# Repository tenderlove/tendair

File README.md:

# Tendair

Tendair is a CO2 / Temp / RH / PM2.5 / VOC / NOx sensor hooked up to an ESP32.

It's basically just [this sensor](https://sensirion.com/media/documents/FAFC548D/693FBB15/PS_DS_SEN6x.pdf)
with [this micro controller](https://www.digikey.com/en/products/detail/espressif-systems/ESP32-C3-WROOM-02-H4/14553033)

Here is a photo:

This is basically just a new version of my [ESP8266 AQ sensor](https://github.com/tenderlove/esp8266aq).

I haven't made an enclosure yet, I'm working on that now.

## Flashing with ESPHome

`esphome.yml` configures the board for [ESPHome](https://esphome.io).
To use the ESP-IDF firmware instead, see [firmware/README.md](firmware/README.md).

Create `secrets.yaml` next to `esphome.yml` with the following keys:

```yaml
wifi_ssid: "your network"
wifi_password: "your wifi password"
api_encryption_key: "output of openssl rand -base64 32"
ap_password: "password for the fallback hotspot"
```

The USB-C port only supplies power, so the first flash goes through a
USB-serial adapter on the 6-pin header. Wire the adapter's TX to the board's
RXD and its RX to TXD, then run:

```
esphome -s name tendair-office run esphome.yml
```

The `-s name` flag sets the device's hostname, which defaults to `tendair`.
Pass the same name on every flash, or the board gets renamed. After the first
flash, `esphome run` can update the board over Wi-Fi.

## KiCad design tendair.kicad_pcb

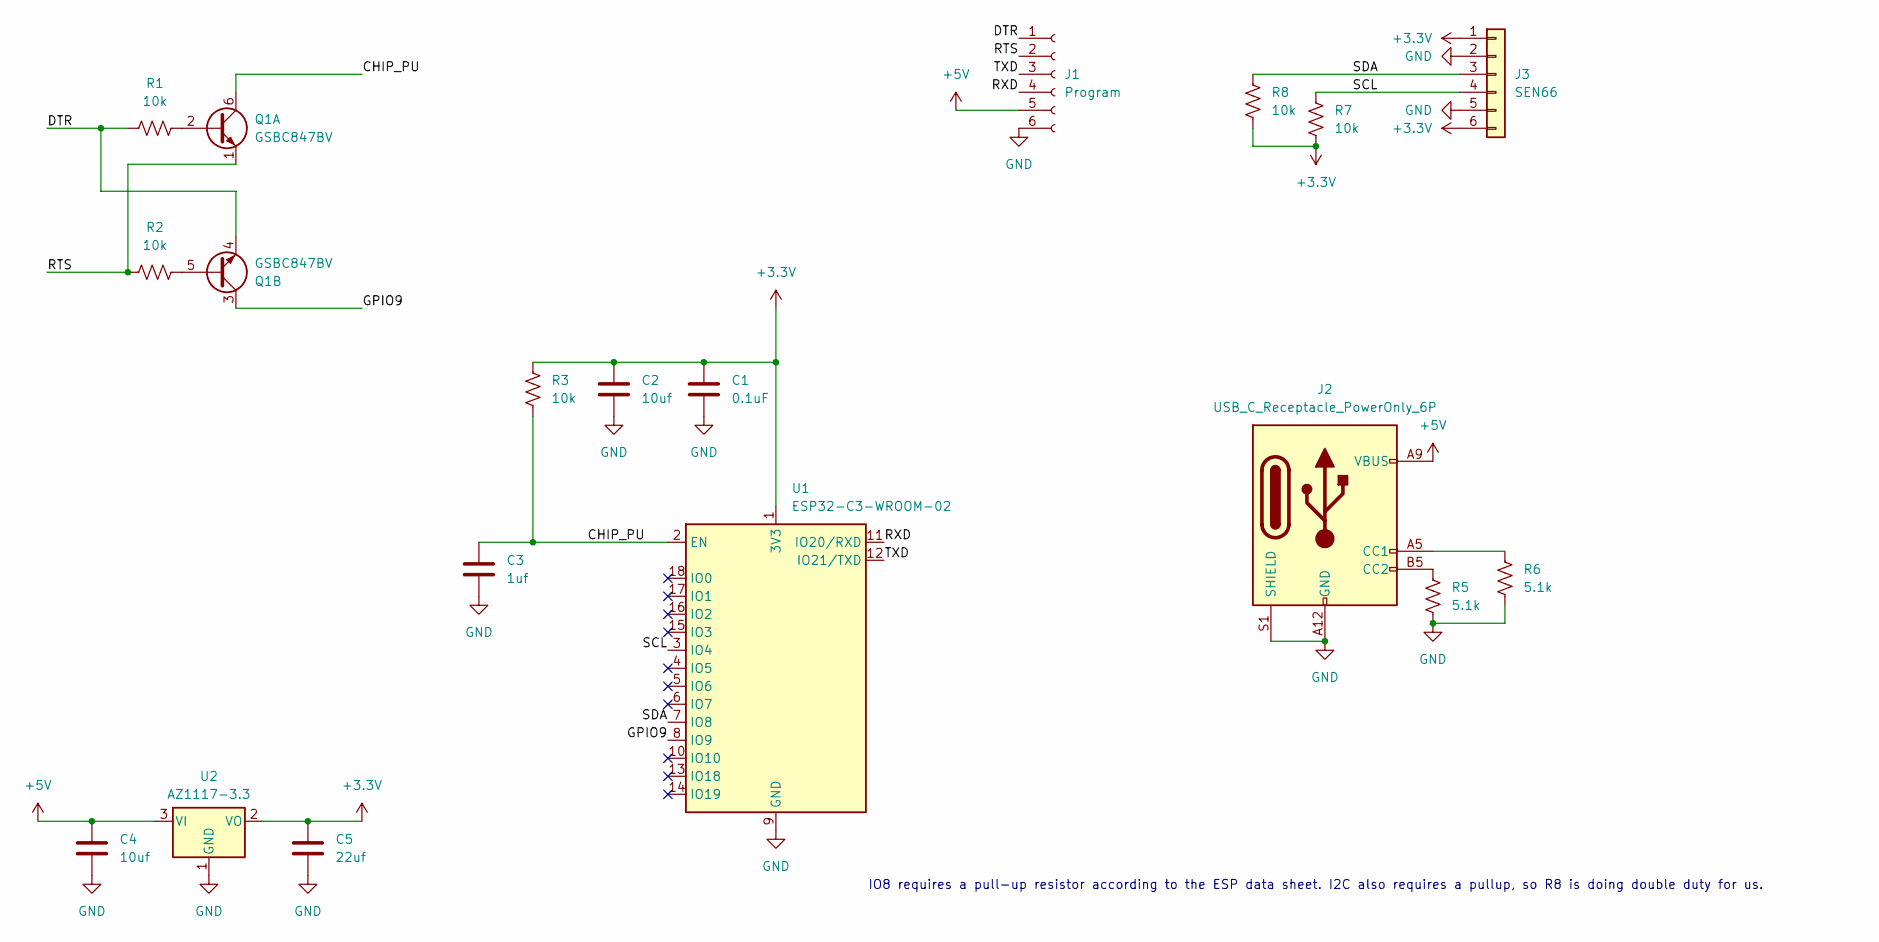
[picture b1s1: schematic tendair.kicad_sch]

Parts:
C1: 0.1uF; C_1206_3216Metric
C2, C4: 10uf; C_1206_3216Metric
C3: 1uf; C_1206_3216Metric
C5: 22uf; C_1206_3216Metric
J1: Program; PinHeader_1x06_P2.54mm_Vertical
J2: USB_C_Receptacle_PowerOnly_6P; USB_C_Receptacle_GCT_USB4125-xx-x_6P_TopMnt_Horizontal
J3: SEN66; JST_GH_SM06B-GHS-TB_1x06-1MP_P1.25mm_Horizontal
Q1: GSBC847BV; SOT-563
R1, R2, R3, R7, R8: 10k; R_1206_3216Metric
R5, R6: 5.1k; R_1206_3216Metric
U1: ESP32-C3-WROOM-02
U2: AZ1117-3.3; SOT-89-3

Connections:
+3.3V: C1.1, C2.1, C5.1, J3.1, J3.6, R3.1, R7.2, R8.2, U1.1 (3V3), U2.2 (VO)
+5V: C4.1, J1.5, J2.A9 (VBUS), J2.B9 (VBUS), U2.3 (VI)
/CHIP_PU: C3.1, Q1.6 (C1), R3.2, U1.2 (EN)
/DTR: J1.1, Q1.4 (E2), R1.1
/GPIO9: Q1.3 (C2), U1.8 (IO9)
/RTS: J1.2, Q1.1 (E1), R2.1
/RXD: J1.4, U1.11 (IO20/RXD)
/SCL: J3.4, R7.1, U1.3 (IO4)
/SDA: J3.3, R8.1, U1.7 (IO8)
/TXD: J1.3, U1.12 (IO21/TXD)
GND: C1.2, C2.2, C3.2, C4.2, C5.2, J1.6, J2.A12 (GND), J2.B12 (GND), J2.S1 (SHIELD), J3.2, J3.5, R5.2, R6.2, U1.9 (GND), U1.19 (GND), U2.1 (GND)
unnamed: J2.A5 (CC1), R6.1
unnamed: J2.B5 (CC2), R5.1
unnamed: Q1.2 (B1), R1.2
unnamed: Q1.5 (B2), R2.2

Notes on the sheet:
IO8 requires a pull-up resistor according to the ESP data sheet. I2C also requires a pullup, so R8 is doing double duty for us.

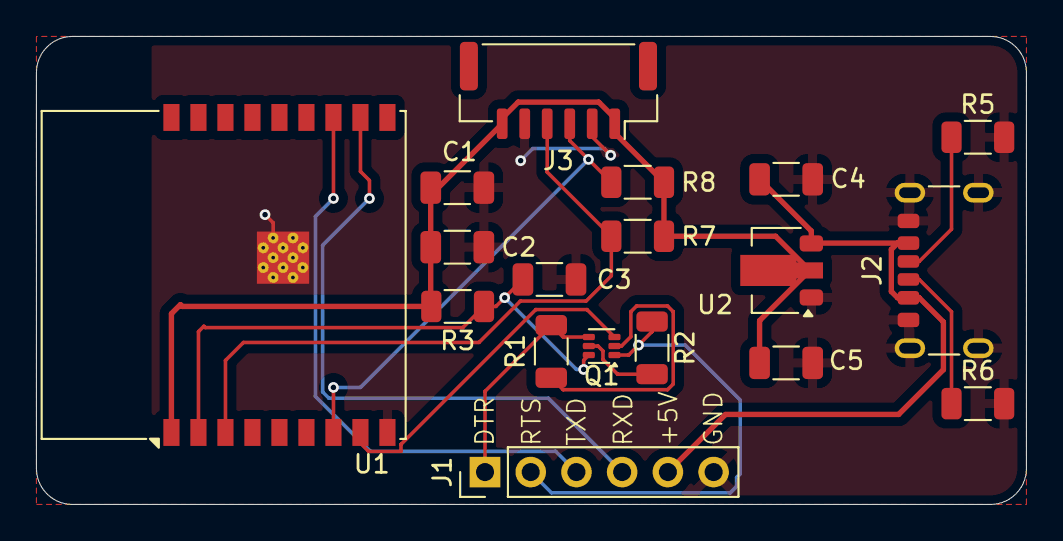
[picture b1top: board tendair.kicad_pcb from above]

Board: 2 copper layers, 55.0 x 26.0 mm, 18 parts (0 on the bottom side), 15 nets.

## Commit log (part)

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2025-11-08 initial schematics
2025-11-09 updating the pcb
2025-11-09 stuff
2025-11-10 seems good!
2025-11-16 adding image
2025-11-16 add license
2025-11-16 update schematic
2025-11-16 adding readme
2025-11-16 add some drawings
2025-11-22 adding bolt posts
2025-11-22 Happy with bolt posts
2025-11-23 Looking better
2025-11-23 Sensiron part seems to fit
2025-11-23 made window
2025-11-23 almost there
2025-11-23 Mostly done. Added Makefile
2025-11-23 add rendered stl files
2025-11-24 this works well!
2025-11-26 set the right uart port
2025-12-05 adding esp-idf project
2025-12-05 import sen66 library
2025-12-05 adding initial wifi / mqtt stuff
2025-12-05 remove sdkconfig
2025-12-05 log all samples via JSON to mqtt
2025-12-05 add the idf components
2025-12-06 add script for putting mqtt in influx
2025-12-06 fix scaled values
2025-12-06 add readme stuff for the firmware
2025-12-24 Don't log info if it's not ready
2025-12-24 lifting the nut up a little
2025-12-24 loop until we have good readings
2026-01-23 udpate for latest pr branch
2026-05-12 fix link
